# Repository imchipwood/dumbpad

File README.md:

dumbpad is a simple macropad with support for up to two rotary encoders, designed to use [QMK](https://qmk.fm/) firmware.

## Gallery

Top two boards are v0.2, bottom two are v0.7. Bottom right is v0.7 with components soldered to the bottom, moving the rotary encoder to the right side.

## In this repository

This repo is separated into five main folders:

- [combo](./combo) houses the main PCB design which includes support for up to two rotary encoders and three status LEDs intended for the Pro Micro.
- [combo_oled](./combo_oled) was created by [KEEBD](https://keebd.com) and replaces the layer LED/Resistors with OLED display support and converted to KiCad.
- [combo_oled_low_profile](./combo_low_profile_oled) Revision of [combo_oled](./combo_oled) with low profile hot swap sockets for Gateron v2 switches
- [combo_teensy](./combo_teensy) is the same as [combo](./combo) but designed for the Teensy2.0.
- [reversible](./reversible) is an older, single-encoder revision using custom reversible Cherry MX sockets to allow the rotary encoder to be moved to the right side.
- [hotswap_rgb - v3.x](./hotswap_rgb) dumbpad featuring per-key RGB and Hotswap sockets

Each folder includes the Eagle or KiCad files as well as exported Gerber files for manufacturing. These folders also include readmes specific to those designs - check them for more info.

## Getting Started
To build your own dumbpad you will need to follow a couple of steps to get started. Described below are the minimal steps you will need to take to to assemble one dumbpad but every board configuration might require different steps. 
#### 1. Choose version. 
You can choose from one of the five different versions shown in the step above.
#### 2. Order your parts. 
Every board needs at least the following components but check the right folder for your parts list.
* 1 x PCB
* 16 x MX-style mechanical switches
* 17 x 1n4148 diodes (thru hole)
* 1 x Arduino Pro Micro or pin-compatible ATmega32u4-based MCU (Or teensy for the teensy version)
* (optional) 1 x EC11 rotary encoder with pushbutton (7-pin)
* (optional) 1 x 6mm tactile switch (to reset MCU)
* LEDS and OLED required for different configurations

#### 3. Assemble your dumbpad
For this step you will need a minimum of a soldering iron and a pair of tweezers
- Solder the diodes, switches, and Arduino Pro Micro (Or teensy) to the PCB

#### 4. Flash your firmware
You can use QMK to create and flash firmware to your dumbpad. You can configure every key to you can use the QMK configurator. Head over to the [QMK configurator](https://config.qmk.fm/#/friedrich/LAYOUT) and select dumbpad/[your version]. Once you have configured your board, click on compile and then on firmware to download the firmware. Check [qmk_firmware/keyboards/dumbpad](https://github.com/qmk/qmk_firmware/tree/master/keyboards/dumbpad) for compiling & uploading instructions

Once you have downloaded a .HEX firmware file we can head over to the [QMK toolbox](https://github.com/qmk/qmk_toolbox/releases) and flash the firmware. Plug in your dumbpad to your computer and set your QMK toolbox to ATmega32U4 for most Arduino Pro Micros. You will need to press your 6mm tacticle switch twice to enter the bootloader, wait for your computer to recognize the dumbpad and click on flash.

### Features

#### Status Indicator LEDs

All PCB revisions in this branch support up to three LEDs.

| LED position on PCB | LED name in QMK software | LED default behavior |
|:-:|:-:|:-:|
| right | LED_00 | 1s bit in binary layer indication |
| center | LED_01 | 2s bit in binary layer indication |
| left | LED_02 | numlock indicator |

LED_00 (right) and LED_01 (center) indicate the layer by displaying the layer number in binary:

| center LED | right LED  |   layer    |
|:----------:|:----------:|:----------:|
| off        | off        | 0 (main)   |
| off        |  on        | 1          |
|  on        | off        | 2          |
|  on        |  on        | 3          |

LED behavior can be changed in the QMK software if you'd like them to do something else. See [v1x.c](https://github.com/imchipwood/qmk_firmware/blob/dumbpad_refactor/keyboards/dumbpad/v1x/v1x.c) for reference.

#### (Optional) Reset Button

[combo](./combo), [hotswap_rgb](./hotswap_rgb) and [reversible](./reversible) have a 6mm switch socket that is optional to include when building your dumbpad. This socket shorts RST to GND to make it easy to enter the bootloader. This is not included in the [combo_teensy](./combo_teensy) design as the Teensy has a reset button already.

If you don't want to solder this switch, make sure to include the [RESET](https://docs.qmk.fm/#/quantum_keycodes) keycode somewhere in your keymap. If you don't include this keycode, you can still enter the bootloader by shorting RST to GND while plugging in the USB cable.

## PCB Dimensions and Cases

97mm x 78.5mm rectangle, with chamfered corners (chamfered edge is 2.828mm long).

There are several cases available for printing, some can be found in `./case`. Another nice case was designed by [f00k3r](https://twitter.com/f00k3r) and uploadead to printables: [Dumbpad Hotswap Case](https://www.printables.com/model/200528-dumbpad-hotswap-case).

### Mounting holes

There are four 2mm holes in a 40mm square centered at (x, y) 58.575mm, 39.425mm. These holes are not plated.

Mounting hole coordinates:

| x (mm) | y (mm) |
|:------:|:------:|
| 38.575 | 19.425 |
| 38.575 | 59.425 |
| 78.575 | 19.425 |
| 78.575 | 59.425 |

## Notes

- In particular, clickable rotary encoders take significantly more force to click than a keyboard switch, so place a rubber foot directly under or at least near any encoders

## Making the PCB

Every parts list includes at least one PCB. You can order a PCb yourself by different manufactures like; [PCB way](https://www.pcbway.com/) or [JLC Pcb](https://jlcpcb.com/) Submit one of the gerber zips from the folder of the type of board you want to make to your preferred manufacturer (or the Eagle .brd file if supported).

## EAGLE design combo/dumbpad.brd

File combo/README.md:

# dumbpad/combo

This folder houses the dumbpad "combo" design - this layout uses custom "combo" Cherry MX + EC11 rotary encoder sockets that allow a single PCB design to support both single- and dual-encoder layouts.

## Compiling QMK

The [QMK Configurator](https://config.qmk.fm/#/dumbpad/v1x/LAYOUT) can compile the various dumbpad versions
with basic rotary encoder support. The default rotary encoder actions are as follows:

| Layer | Clockwise | Counter-clockwise |
|:-:|:-:|:-:|
| 1 | KC_MS_R (move mouse right) | KC_MS_L (move mouse left) |
| 2 | KC_EQUALS (Adobe "increase") | KC_MINUS (Adobe "decrease") |

If you want the encoder to do something else, you will need to clone the [qmk_firmare](https://github.com/qmk/qmk_firmware) repository and modify the rotary encoder code. The [QMK docs](https://docs.qmk.fm/#/newbs) can help you with this.

## Eagle PCB render

## Case

A case is available on [Thingiverse](https://www.thingiverse.com/thing:4816409) - thanks to Anthony @ [customkbd.com](http://customkbd.com.au/) for the initial design and being kind enough to send the original design files!

## Single- vs Dual-Encoder Support

The combined Cherry MX/encoder sockets allow single- and dual-encoder configurations.

The only rule when using two encoders is that there cannot be two encoders on the left side at once, or two on the right side.
This table shows where the encoders are in the switch grid ("X" for encoder, "s" for switch):

| C0  | C1  | C2  | C3  | C4  |
|:---:|:---:|:---:|:---:|:---:|
|     |__X__|  s  |  s  |__X__|
|     |  s  |  s  |  s  |  s  |
|     |  s  |  s  |  s  |  s  |
|__X__|__X__|  s  |  s  |__X__|

- The three encoders in columns C0 and C1 are connected to each other
- The two encoders in column C4 are connected to each other

So, if doing dual encoders, one must be in column C4 and the other in either C0 or C1. Three or more encoders will not work.

The following sections describe the configurations that the default keymaps in QMK are designed for.

### Single-Encoder (Default Configuration)

In the default configuration, the encoder is in column 0, the bottom left corner below the Pro Micro. All other sockets are filled with switches.

| C0  | C1  | C2  | C3  | C4  |
|:---:|:---:|:---:|:---:|:---:|
|     |  s  |  s  |  s  |  s  |
|     |  s  |  s  |  s  |  s  |
|     |  s  |  s  |  s  |  s  |
|__X__|  s  |  s  |  s  |  s  |

### Dual-Encoder Bottom

One dual-encoder configuration has encoders in the bottom two corners of the 4x4 grid, and switches in the rest of the grid. The socket in column 0 is left empty.

| C0  | C1  | C2  | C3  | C4  |
|:---:|:---:|:---:|:---:|:---:|
|     |  s  |  s  |  s  |  s  |
|     |  s  |  s  |  s  |  s  |
|     |  s  |  s  |  s  |  s  |
|     |__X__|  s  |  s  |__X__|

### Dual-Encoder Top

Another dual-encoder configuration has encoders in the top two corners of the 4x4 grid, and switches in the rest of the grid. The socket in column 0 is left empty.

| C0  | C1  | C2  | C3  | C4  |
|:---:|:---:|:---:|:---:|:---:|
|     |__X__|  s  |  s  |__X__|
|     |  s  |  s  |  s  |  s  |
|     |  s  |  s  |  s  |  s  |
|     |  s  |  s  |  s  |  s  |

### No-Encoder

You may also choose not to use any rotary encoders if you like!

### Bill Of Materials

- 1 x PCB
- 16 x MX-style mechanical switches
- 17 x 1n4148 diodes (thru hole)
- 1 x Arduino Pro Micro or pin-compatible ATmega32u4-based MCU (Or teensy for the teensy version)
- 1x or 2x EC11 rotary encoder with pushbutton (7-pin)
- (optional) 1 x 6mm tactile switch (to reset MCU)
- (optional) 3x 3mm resistors (for limiting current in LEDs)

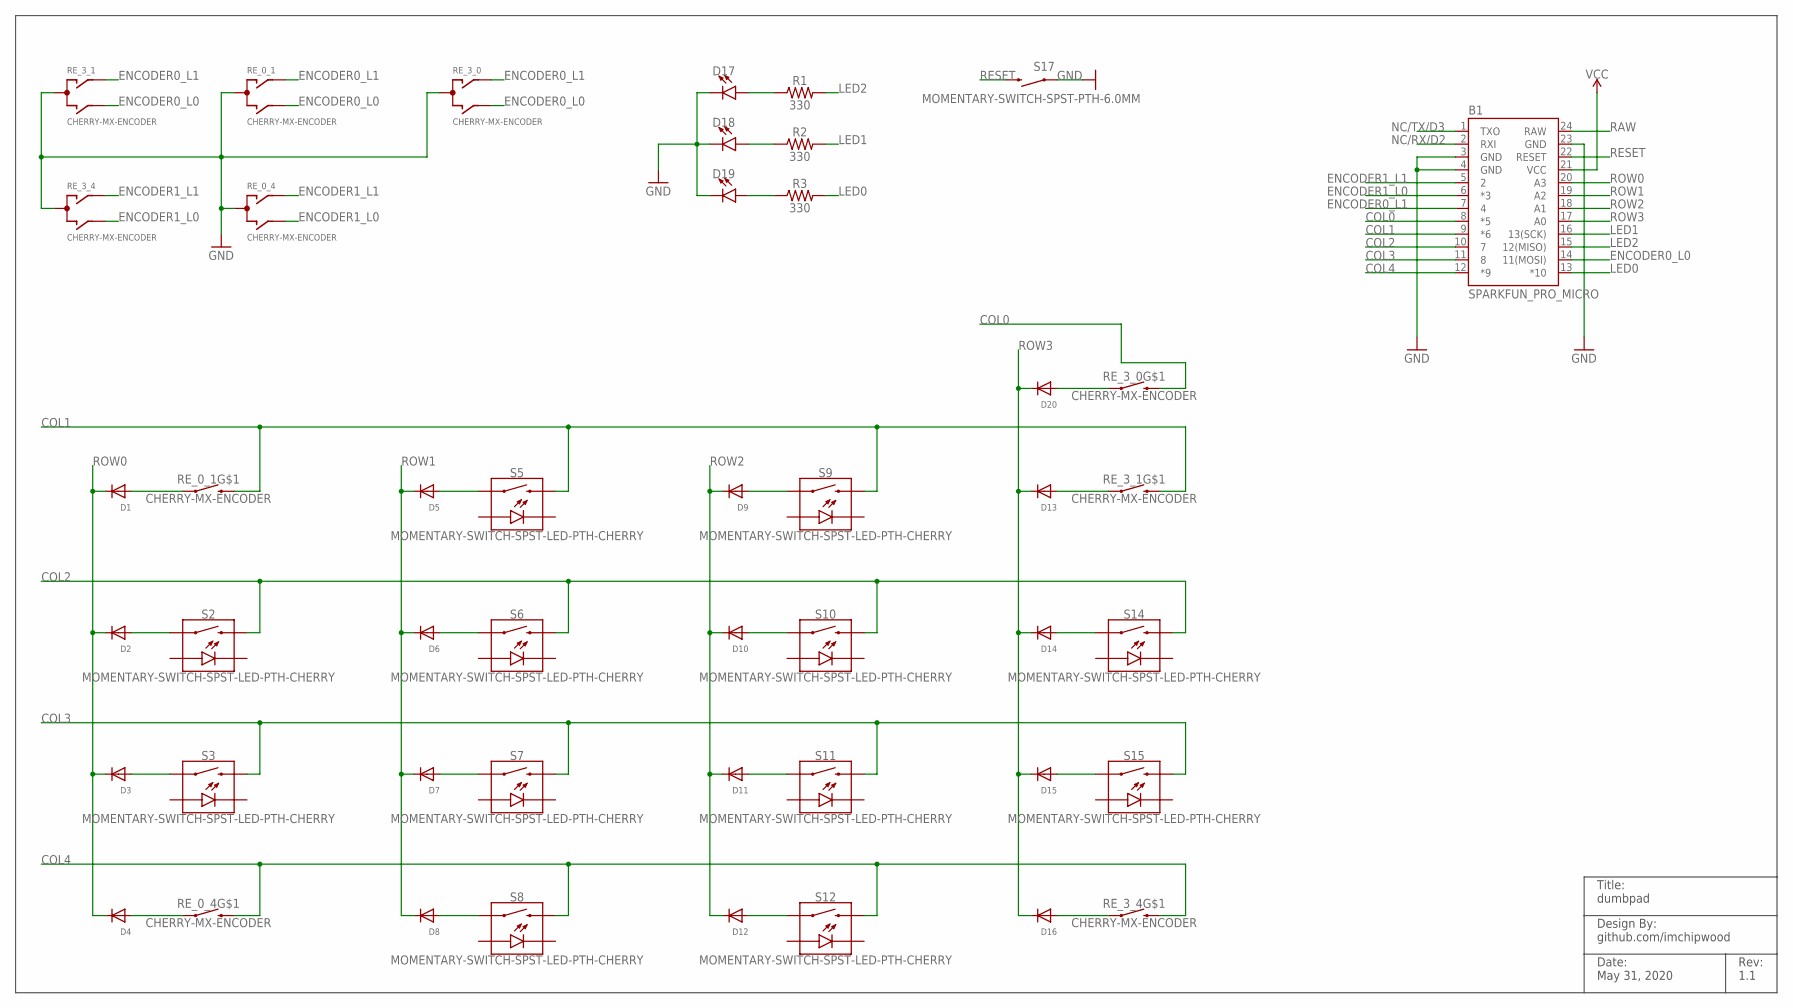
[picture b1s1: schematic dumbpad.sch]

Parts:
B1: SPARKFUN_PRO_MICRO
D1, D2, D3, D4, D5, D6, D7, D8, D9, D10, D11, D12, D13, D14, D15, D16, D20: DIODEDO-1N4148; DO-1N4148
D17, D18, D19: LED3MM; LED_3MM
R1, R2, R3: 330; AXIAL-0.3
RE_0_1, RE_0_4, RE_3_0, RE_3_1, RE_3_4: CHERRY-MX-ENCODER
S2, S3, S5, S6, S7, S8, S9, S10, S11, S12, S14, S15: MOMENTARY-SWITCH-SPST-LED-PTH-CHERRY; CHERRY-MX-LED
S17: MOMENTARY-SWITCH-SPST-PTH-6.0MM; TACTILE_SWITCH_PTH_6.0MM

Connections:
COL0: B1.8 (*5), RE_3_0.E (2), RE_3_0.S2 (2)
COL1: B1.9 (*6), RE_0_1.E (2), RE_0_1.S2 (2), RE_3_1.E (2), RE_3_1.S2 (2), S5.S2 (2), S9.S2 (2)
COL2: B1.10 (7), S2.S2 (2), S6.S2 (2), S10.S2 (2), S14.S2 (2)
COL3: B1.11 (8), S3.S2 (2), S7.S2 (2), S11.S2 (2), S15.S2 (2)
COL4: B1.12 (*9), RE_0_4.E (2), RE_0_4.S2 (2), RE_3_4.E (2), RE_3_4.S2 (2), S8.S2 (2), S12.S2 (2)
ENCODER0_L0: B1.14 (11(MOSI)), RE_0_1.B, RE_3_0.B, RE_3_1.B
ENCODER0_L1: B1.7 (4), RE_0_1.A, RE_3_0.A, RE_3_1.A
ENCODER1_L0: B1.6 (*3), RE_0_4.B, RE_3_4.B
ENCODER1_L1: B1.5 (2), RE_0_4.A, RE_3_4.A
GND: B1.3 (GND), B1.4 (GND), B1.23 (GND), D17.K (C), D18.K (C), D19.K (C), RE_0_1.C, RE_0_4.C, RE_3_0.C, RE_3_1.C, RE_3_4.C, S17.1
LED0: B1.13 (*10), R3.P$2 (2)
LED1: B1.16 (13(SCK)), R2.P$2 (2)
LED2: B1.15 (12(MISO)), R1.P$2 (2)
unnamed: D4.A, RE_0_4.D (1), RE_0_4.S1 (1)
unnamed: D3.A, S3.S1 (1)
unnamed: D2.A, S2.S1 (1)
unnamed: D1.A, RE_0_1.D (1), RE_0_1.S1 (1)
unnamed: D17.A, R1.P$1 (1)
unnamed: D8.A, S8.S1 (1)
unnamed: D7.A, S7.S1 (1)
unnamed: D6.A, S6.S1 (1)
unnamed: D5.A, S5.S1 (1)
unnamed: D18.A, R2.P$1 (1)
unnamed: D16.A, RE_3_4.D (1), RE_3_4.S1 (1)
unnamed: D15.A, S15.S1 (1)
unnamed: D14.A, S14.S1 (1)
unnamed: D13.A, RE_3_1.D (1), RE_3_1.S1 (1)
unnamed: D19.A, R3.P$1 (1)
unnamed: D12.A, S12.S1 (1)
unnamed: D11.A, S11.S1 (1)
unnamed: D10.A, S10.S1 (1)
unnamed: D9.A, S9.S1 (1)
unnamed: D20.A, RE_3_0.D (1), RE_3_0.S1 (1)
NC/RX/D2: B1.2 (RXI)
NC/TX/D3: B1.1 (TXO)
RAW: B1.24 (RAW)
RESET: B1.22 (RESET), S17.3 (2)
ROW0: B1.20 (A3), D1.C, D2.C, D3.C, D4.C
ROW1: B1.19 (A2), D5.C, D6.C, D7.C, D8.C
ROW2: B1.18 (A1), D9.C, D10.C, D11.C, D12.C
ROW3: B1.17 (A0), D13.C, D14.C, D15.C, D16.C, D20.C
VCC: B1.21 (VCC)

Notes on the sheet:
Rev: 1.1
Date: May 31, 2020
Design By: github.com/imchipwood
Title: dumbpad

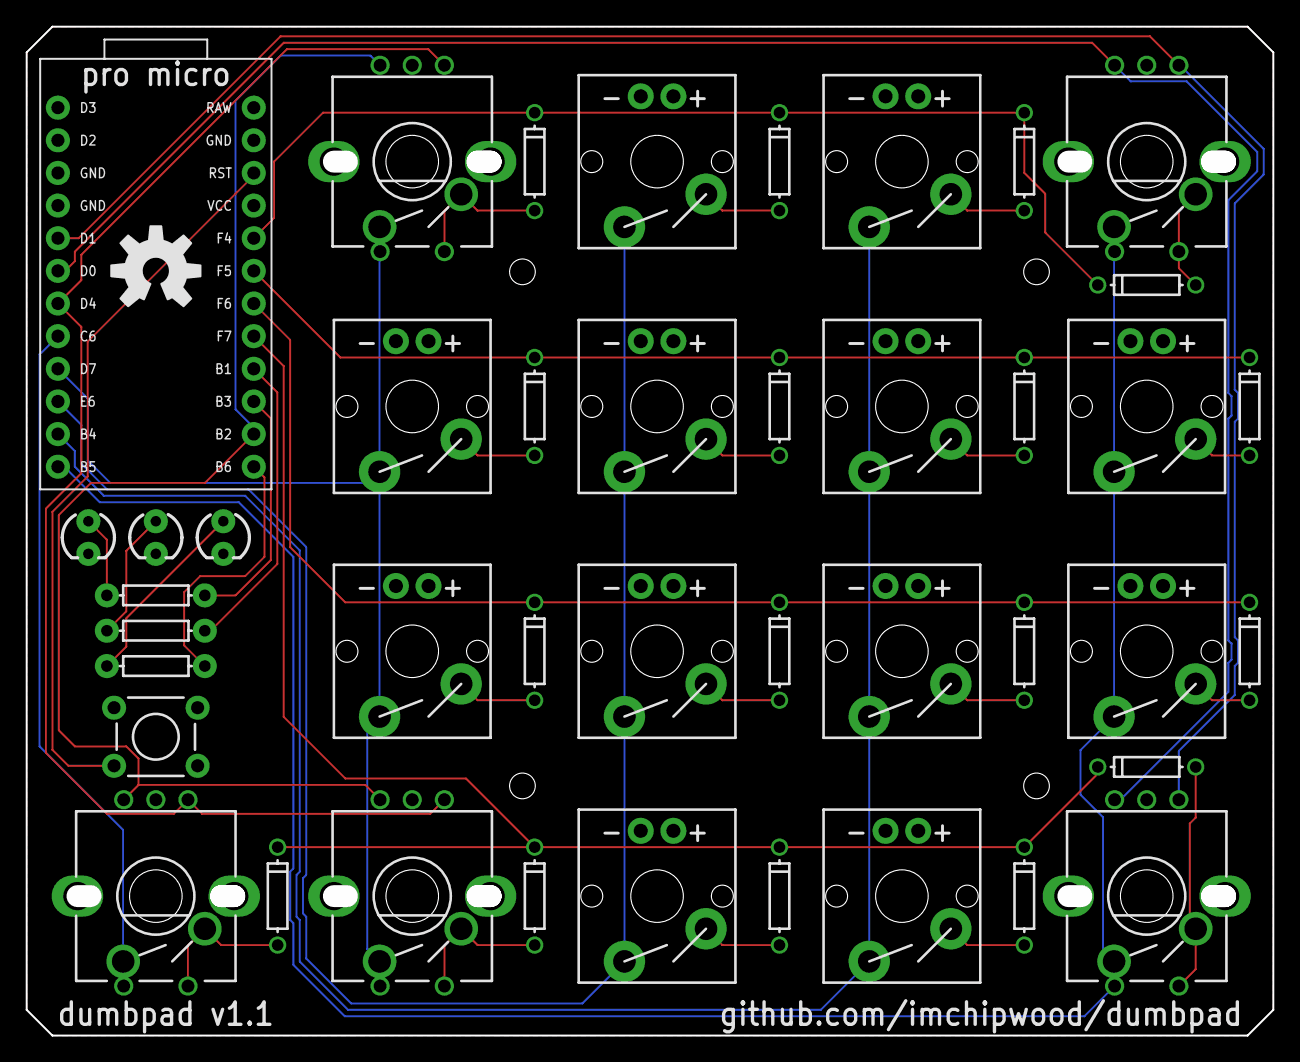
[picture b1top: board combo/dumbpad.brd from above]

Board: 2 copper layers, 95.4 x 76.9 mm, 44 parts (1 on the bottom side), 38 nets.

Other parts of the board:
LOGO1, LOGO2: OSHW-LOGOL; OSHW-LOGO-L

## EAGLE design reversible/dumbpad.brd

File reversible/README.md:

# dumbpad
Designed by [imchipwood](https://www.github.com/imchipwood) in Portland, Oregon, USA

Special thanks to [QMK](https://qmk.fm/) for open-source keyboard firmware

## Description
dumbpad is a simple 4x4 numpad with a rotary encoder. It is designed for the ATmega32u4-based Pro Micro but any ATmega32u4-based microcontroller using the same form factor should work

It is designed to run [QMK firmware](https://github.com/qmk/qmk_firmware) - check [qmk_firmware/keyboards/dumbpad](https://github.com/qmk/qmk_firmware/tree/master/keyboards/dumbpad) for compiling & uploading instructions

### Revisions
- v0.5 introduces 2x LEDs for indicating which layer is enabled, accurately representing up to 4 layers
- v0.6_dualencoder is a true 4x4 macropad with two rotary encoders - one in each bottom corner
- v0.6_dualencoder_top is the same as v0.6_dualencoder but the encoders are moved to the top corners
- v0.7 PCB is flippable. Two jumpers must be soldered:
  - Encoder on left (default layout) - solder the left side of the jumpers to the center
  - Encoder on right (PCB upside down) - solder the right side of the jumpers to the center
- v1.0 PCB adds a 3rd LED - default use is to indicate if NUMLOCK is on

#### dumbpad v0.2 (top) & v0.7 (bottom), PCB by [OSH Park](https://www.oshpark.com)

#### Dual-encoder version by chicocode:

#### Eagle PCB render

### Bill of materials
* 16x Cherry-style mechanical switches
* 17x 1n4148 diodes (thru hole)
* 1x Arduino Pro Micro or pin-compatible ATmega32u4-based MCU
* 1x EC11 rotary encoder with pushbutton (7-pin)
* (optional) 1x 6mm tactile switch (to reset MCU)
* (optional) 3x 3mm LEDs (whatever color)
* (optional) 3x 330ohm or similar resistors for the LEDS (not needed if not adding LEDs)

#### Notes
- No case is currently available, but v1.0 has 2mm mounting holes in a 40mm square centered at x=58.575mm, y=39.425mm (from the bottom left)
  - 38.575, 19.425
  - 38.575, 59.425
  - 78.575, 19.425
  - 78.575, 59.425
- To avoid damaging the PCB and prevent it from sliding around, put rubber feet on the bottom of the PCB
  - place feet directly under the rotary encoder(s) as they take significant force to press
  - place the others in the corners and one in the center

## Making the PCB
Submit the `.brd` file to your preferred PCB manufacturer - be mindful of minimum quantity requirements.

### OSH Park - USA PCB Manufacturing
Shameless Portland, Oregon company plug - [OSH Park](https://www.oshpark.com) is a fast and reliable manufacturer, combining multiple individual orders into a single panel to minimize end-user costs. dumbpad is just under $60 for 3 copies through OSH Park.

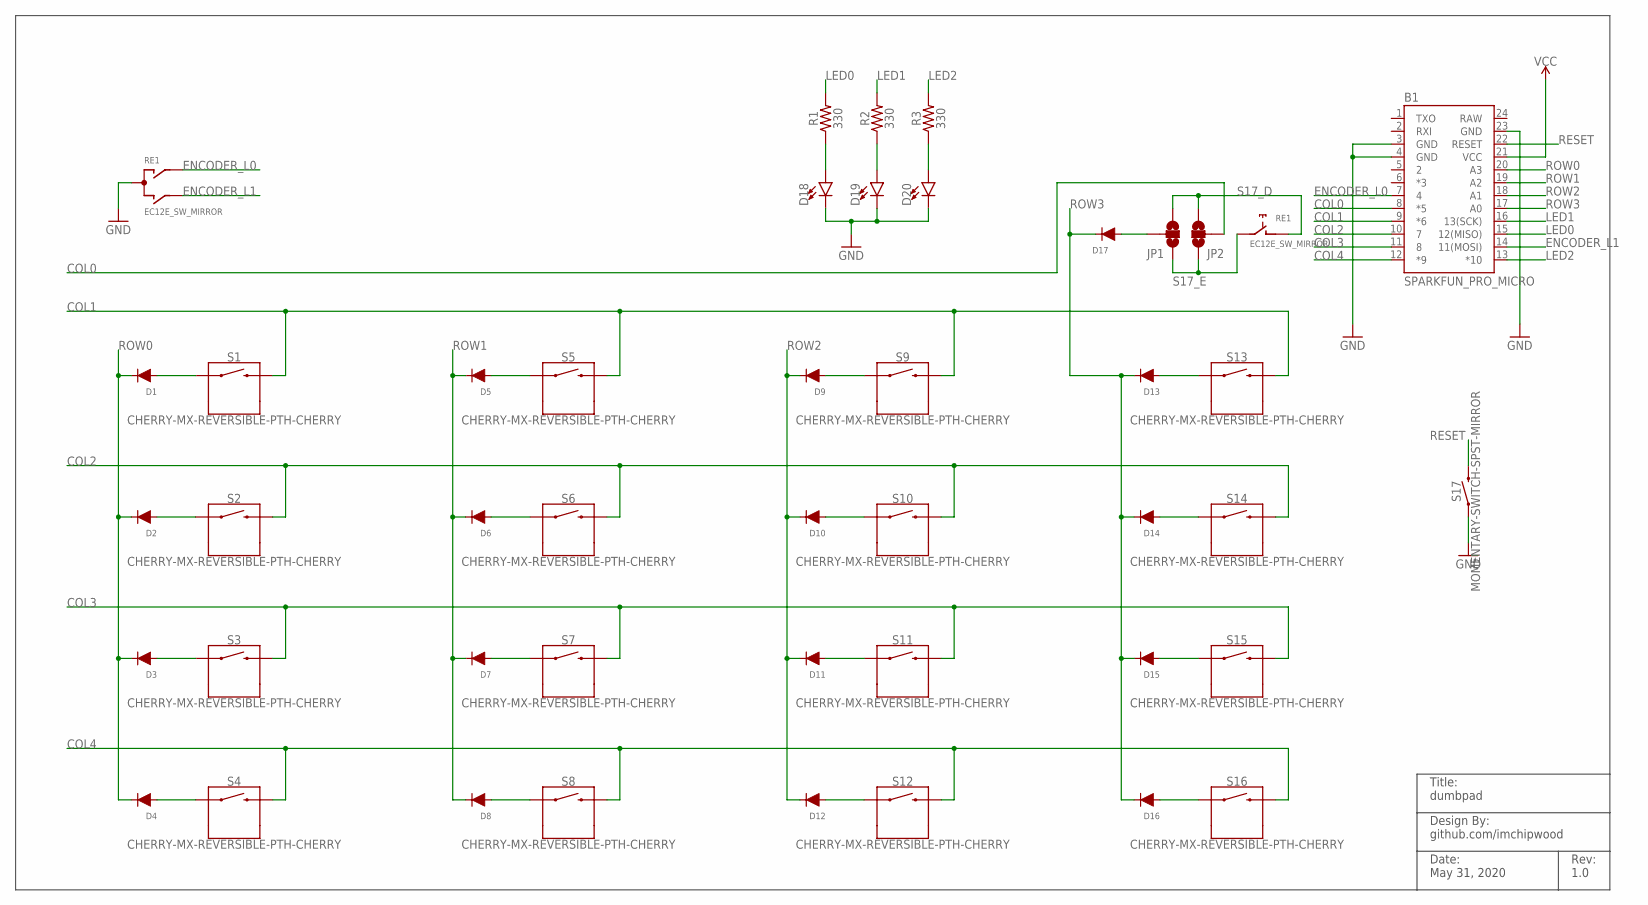
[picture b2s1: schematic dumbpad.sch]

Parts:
B1: SPARKFUN_PRO_MICRO
D1, D2, D3, D4, D5, D6, D7, D8, D9, D10, D11, D12, D13, D14, D15, D16, D17: DO-1N4148_MIRROR
D18, D19, D20: LED3MM; LED_3MM
JP1, JP2: JUMPER-SMT_3_NO_NO_SILK; SMT-JUMPER_3_0-NO_TRACE_NO-SILK
R1, R2, R3: 330; AXIAL-0.3_MIRROR
RE1: EC12E_SW_MIRROR; ALPS_EC12E_SW_MIRROR
S1, S2, S3, S4, S5, S6, S7, S8, S9, S10, S11, S12, S13, S14, S15, S16: CHERRY-MX-REVERSIBLE-PTH-CHERRY; CHERRY-MX-REVERSIBLE
S17: MOMENTARY-SWITCH-SPST-MIRROR; TACTILE_SWITCH_PTH_6.0MM_MIRROR

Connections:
COL0: B1.8 (*5), JP2.2
COL1: B1.9 (*6), S1.S2_0 (2), S1.S2_1 (2), S5.S2_0 (2), S5.S2_1 (2), S9.S2_0 (2), S9.S2_1 (2), S13.S2_0 (2), S13.S2_1 (2)
COL2: B1.10 (7), S2.S2_0 (2), S2.S2_1 (2), S6.S2_0 (2), S6.S2_1 (2), S10.S2_0 (2), S10.S2_1 (2), S14.S2_0 (2), S14.S2_1 (2)
COL3: B1.11 (8), S3.S2_0 (2), S3.S2_1 (2), S7.S2_0 (2), S7.S2_1 (2), S11.S2_0 (2), S11.S2_1 (2), S15.S2_0 (2), S15.S2_1 (2)
COL4: B1.12 (*9), S4.S2_0 (2), S4.S2_1 (2), S8.S2_0 (2), S8.S2_1 (2), S12.S2_0 (2), S12.S2_1 (2), S16.S2_0 (2), S16.S2_1 (2)
ENCODER_L0: B1.7 (4), RE1.A
ENCODER_L1: B1.14 (11(MOSI)), RE1.B
GND: B1.3 (GND), B1.4 (GND), B1.23 (GND), D18.K (C), D19.K (C), D20.K (C), RE1.C, S17.1
LED0: B1.15 (12(MISO)), R1.P$2 (2)
LED1: B1.16 (13(SCK)), R2.P$2 (2)
LED2: B1.13 (*10), R3.P$2 (2)
unnamed: D4.A, S4.S1_0 (1), S4.S1_1 (1)
unnamed: D3.A, S3.S1_0 (1), S3.S1_1 (1)
unnamed: D2.A, S2.S1_0 (1), S2.S1_1 (1)
unnamed: D1.A, S1.S1_0 (1), S1.S1_1 (1)
unnamed: D18.A, R1.P$1 (1)
unnamed: D8.A, S8.S1_0 (1), S8.S1_1 (1)
unnamed: D7.A, S7.S1_0 (1), S7.S1_1 (1)
unnamed: D6.A, S6.S1_0 (1), S6.S1_1 (1)
unnamed: D5.A, S5.S1_0 (1), S5.S1_1 (1)
unnamed: D20.A, R3.P$1 (1)
unnamed: D16.A, S16.S1_0 (1), S16.S1_1 (1)
unnamed: D15.A, S15.S1_0 (1), S15.S1_1 (1)
unnamed: D14.A, S14.S1_0 (1), S14.S1_1 (1)
unnamed: D13.A, S13.S1_0 (1), S13.S1_1 (1)
unnamed: D19.A, R2.P$1 (1)
unnamed: D12.A, S12.S1_0 (1), S12.S1_1 (1)
unnamed: D11.A, S11.S1_0 (1), S11.S1_1 (1)
unnamed: D10.A, S10.S1_0 (1), S10.S1_1 (1)
unnamed: D9.A, S9.S1_0 (1), S9.S1_1 (1)
RAW: B1.24 (RAW)
RESET: B1.22 (RESET), S17.2
ROW0: B1.20 (A3), D1.C, D2.C, D3.C, D4.C
ROW1: B1.19 (A2), D5.C, D6.C, D7.C, D8.C
ROW2: B1.18 (A1), D9.C, D10.C, D11.C, D12.C
ROW3: B1.17 (A0), D13.C, D14.C, D15.C, D16.C, D17.C
ROW3_A: D17.A, JP1.2
S17_D: JP1.1, JP2.3, RE1.D (1)
S17_E: JP1.3, JP2.1, RE1.E (2)
VCC: B1.21 (VCC)

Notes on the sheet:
Rev: 1.0
Date: May 31, 2020
Design By: github.com/imchipwood
Title: dumbpad

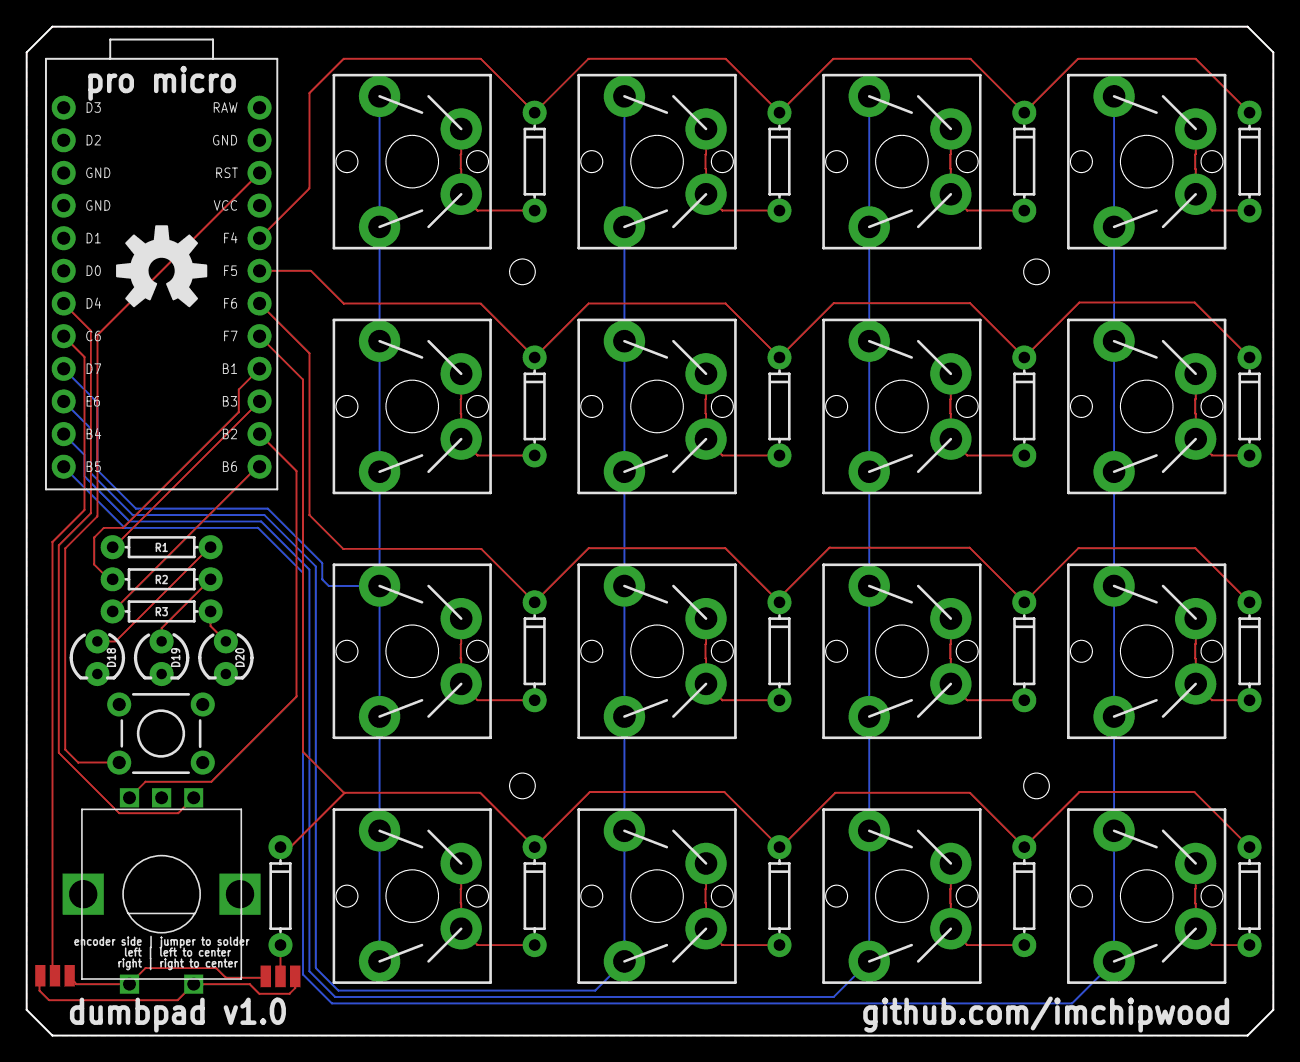
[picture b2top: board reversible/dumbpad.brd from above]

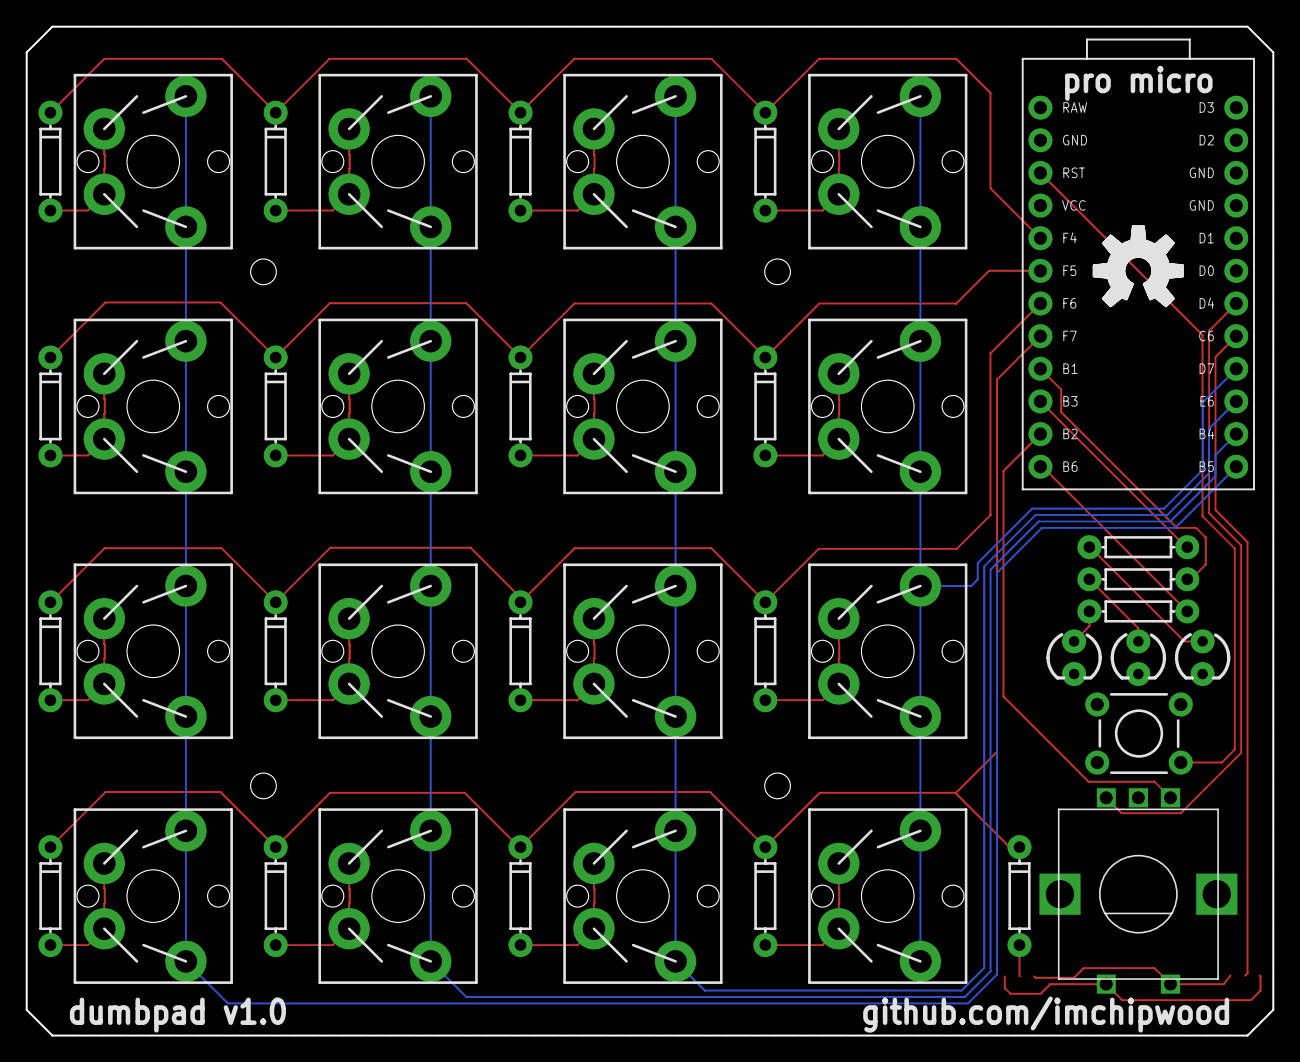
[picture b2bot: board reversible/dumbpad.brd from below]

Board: 2 copper layers, 97.0 x 78.5 mm, 47 parts (2 on the bottom side), 38 nets.

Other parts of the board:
LOGO1, LOGO2, LOGO3: OSHW-LOGOL; OSHW-LOGO-L

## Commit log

2019-07-03 adding readme
2019-07-14 diodes...
2019-07-14 tweaks
2019-07-14 moved email/name thing
2019-07-14 added reset button, centered diodes on switches
2019-07-14 ignore eagle temp files
2019-07-14 updated README with switch
2019-07-14 minor tweaks, sch as png
2019-07-14 name/contact info on both sides, some pro micro pins labeled to ensure it's not mounted incorrectly
2019-07-14 added labels to all pro micro pins
2019-07-14 shrinking, aligning
2019-07-14 removed resistors from rotary encoder, updated readme
2019-07-28 moved all components to top, rerouted
2019-07-28 slight tweaks to spacing, orientation of one diode, etc.
2019-07-28 v0.4 done - moved diodes to right side of switches for cleaner routing. Adjusted dimension slightly to give more room around switches so keycaps don't hang over the sides
2019-07-28 updated readme with image and some other info
2019-07-28 whoops messed up markdown image
2019-07-28 added GPL
2019-07-28 updated gitignore
2019-07-28 more tweaks to v4 for A E S T H E T I C
2019-07-29 who doesn't like LEDs
2019-08-03 final touches to v0.5
2019-08-03 updated readme for v0.5 - 2x LEDs, 2x resistors
2019-08-04 added Open Source Hardware logo to tplace and bplace
2019-08-04 added screenshot to readme
2019-08-04 added screenshot of layout and put it in the readme
2019-08-04 removed top OSHW silk, adding reset button back shortly
2019-08-04 added reset button back to v0.5
2019-08-04 minor tweak to routing
2019-08-05 way too many vias... but it's routed
2019-08-06 some rerouting to reduce vias and clean things up a tad
2019-08-06 updated readme and screenshot
2019-08-06 added LEDs to README
2019-08-30 dual encoders on the bottom, need to add mirror switches
2019-08-30 updated readme, added reversible switch sockets so PCB can be soldered to from either side
2019-08-30 merging v05 into master manually
2019-08-30 using reversible sockets
2020-01-18 moved encoders to the top
2020-01-18 updated board screenshot
2020-03-20 added dual-encoder image from someone who actually made one
2020-04-11 added jumpers for reversing encoder when using encoder on right side instead of left
2020-04-11 updated revision to v0.7
2020-04-12 merging v08_jumpers to master
2020-04-15 updated readme and added board layout screenshot
2020-04-15 updated README and added screenshot of board layout
2020-04-15 updated v0.5 readme
2020-04-15 fixed error in readme
2020-04-15 moved some wires to avoid sketchy tolerances and updated readme
2020-04-15 replaced reversible sockets with normal cherry sockets, rerouted some stuff, updated readme and screenshot
2020-04-22 added 3rd LED for numlock indication
2020-04-24 moved LEDs, added more gs
2020-04-24 made reversible sockets show outline on tplace and bplace
2020-04-29 updated readme, made jumpers a little bigger for easier soldering, updated version to 1.0
2020-05-02 swapped some LED pins to make the first two LEDs connecting to the same pins as v0.x PCBs
2020-05-06 all parts have bottom silk screen now, rerouted some stuff
2020-05-06 added mounting holes
2020-05-06 added notes to readme about mounting holes
2020-05-06 fixed issue with wrong jumper size
2020-05-06 replaced image in readme
2020-05-07 v1.0 dual encoder version with debug headers
2020-05-17 non-debug version of dualencoder layout
2020-05-17 minor tweaks
2020-05-17 changed mounting holes to 40mm square
2020-05-17 changed mounting holes to 40mm
2020-05-17 updated readme for mounting holes
2020-05-17 readme formatting fix
2020-05-21 dualencoder now has cherry/encoder sockets for putting encoders on either top row or bottom row
2020-05-21 dual + single encoder configuration
2020-05-21 updating board and adding cam file
2020-05-21 updating gitignore, updating board png
2020-05-21 minor changes
2020-05-22 long pads with mill
2020-05-22 rerouted some stuff
2020-05-22 organized schematic, silkscreen tweaks,
2020-05-22 rerouted and moved things around, updated readme
2020-05-30 gerbers for v1.0 board
2020-05-30 adding gerbers, got slots working, updated readme
2020-05-30 removed cam file, v1.0 gerbers
2020-05-30 removed bottomsilk screenshot
2020-05-31 master now contains all variations of the board, organized into their own folders
2020-05-31 updated readmes and whatnot
2020-05-31 forgot to save readme...
2020-06-01 updated library for combo_teensy
2020-06-01 added gerbers for teensy
2020-06-01 added some images of the possible layouts to combo/README.md
2020-06-01 fixing bad merge
2020-06-01 fixing naming issue in combo
2020-06-01 matching reversible version encoder pins to combo
2020-06-01 fixed encoder pin naming mismatch, updated screenshot
2020-06-01 updated combo gerbers
2020-06-01 updated reversible gerbers
2021-04-01 copying initial case files from other repo
2021-04-01 updated case to have slight relief for usb cable
2021-04-02 adding embossed version
2021-04-04 Fixing qmk links
2021-04-04 updated usb port relief area
2021-04-04 updated combo readme
2021-04-04 updated readme, removed unused stl
2021-04-04 added thingiverse link to case to readmes
2021-04-04 fixed thingiverse link
2021-09-22 added plate stl files & plate readme
2021-09-22 added stl files and readme for plates
2021-09-22 added thingiverse link to readme
2021-09-23 updated plate thickness
2022-01-22 convert from Eagle to KiCad and replaced LEDs for OLED Display
2022-01-22 added combo_oled designed by KEEBD to the README
2022-02-09 Dumbpad with RGB and Hotswap
2022-02-09 v3.x: Add Gerberfiles
2022-02-11 Update images
2022-02-18 Dumbpad v3: cleanup dependencies
2022-04-03 Add VIA configuration for dumbpad v3
2022-04-26 Add README with images and info for the Dumbpad OLED
2022-04-26 settings adjustments
2022-04-26 Add Firmware details to dumbpad_oled README
2022-04-28 fix schematic and remove missing drawing sheet
2022-04-28 changed the USB cable relief slightly - less depth, looking to rest the cable on the case a bit (have had some troubles with the micro USB port eventually falling off on my oldest dumbpads)
2022-04-29 add missing mounting holes from the conversion
2022-04-29 update gerber zip with change adding mount holes back
2022-05-09 Add notes to Case Options
2022-05-23 Fix link to full plate stl
2022-10-11 feat: add firmware and update readme.md
2023-01-31 Fixed spelling on line 44
    Line 44 had the spelling baord, fixed it to board
2024-05-21 added note regarding non-plated through-holes
    ... which will potentially throw red flags for manufacturers
2024-06-19 Added new case designs
2026-03-03 Added images for completed keypad v1.3.1
2026-03-03 Readme wording.
2026-06-26 fix typo: reconize -> recognize in README.md

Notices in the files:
parts and their libraries:
SparkFun-Boards: Licensing: Creative Commons ShareAlike 4.0 International - https://creativecommons.org/licenses/by-sa/4.0
